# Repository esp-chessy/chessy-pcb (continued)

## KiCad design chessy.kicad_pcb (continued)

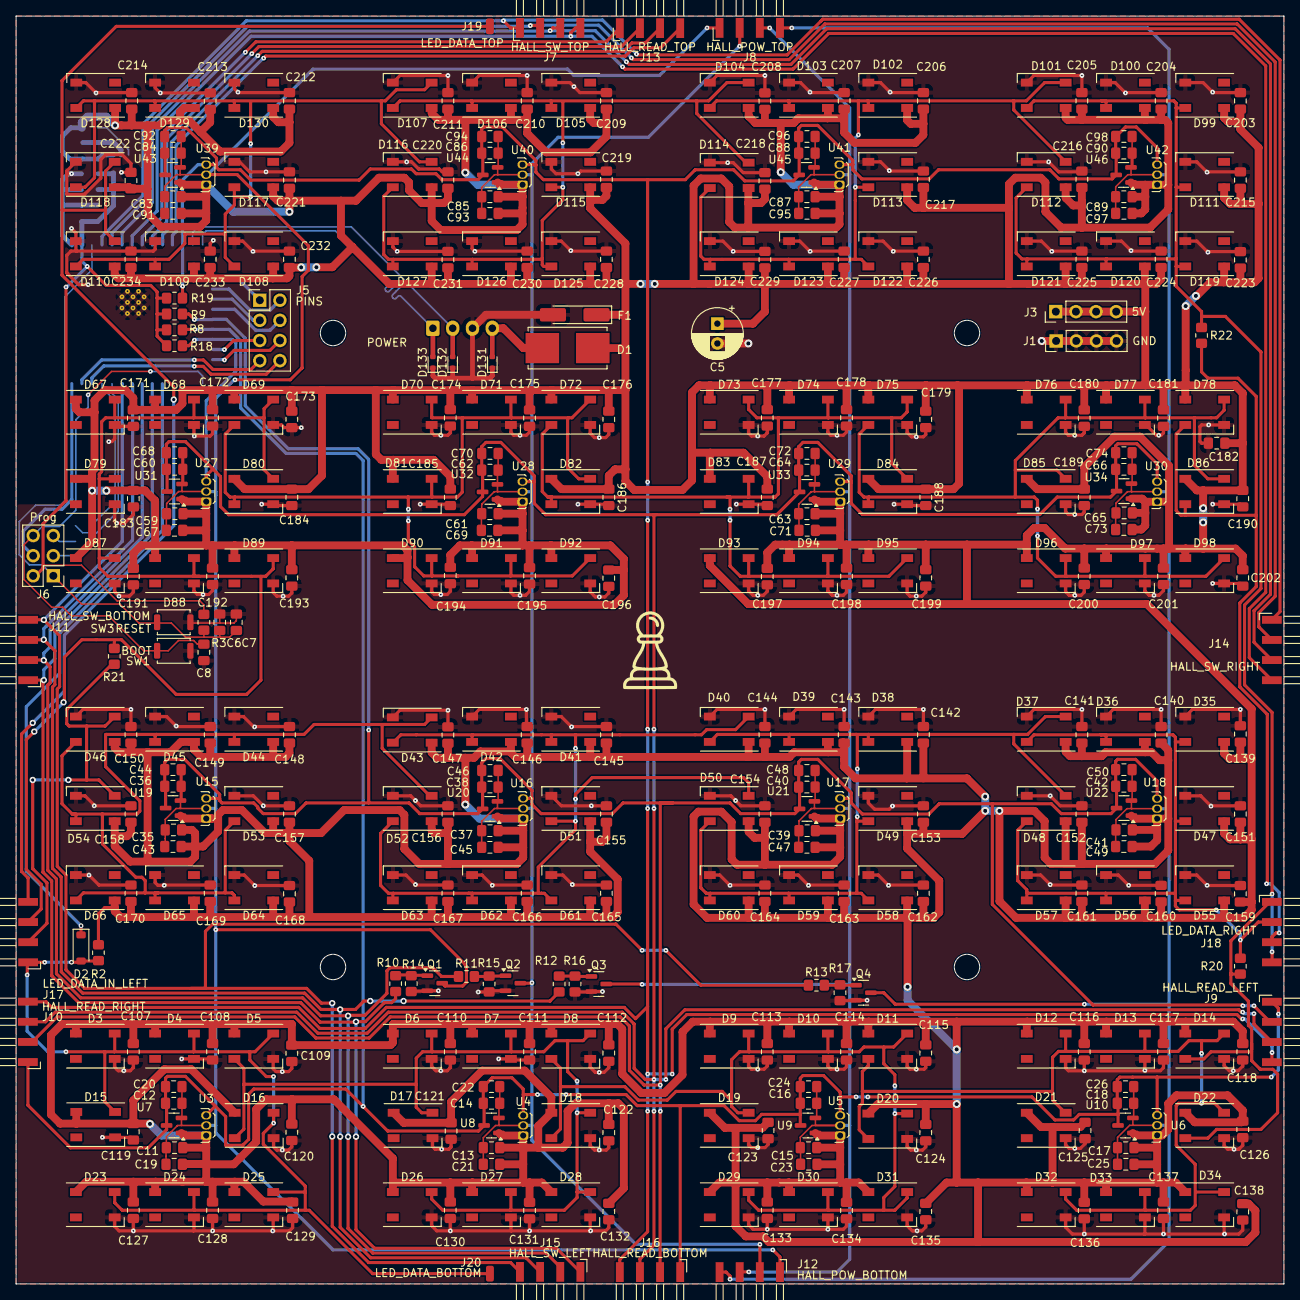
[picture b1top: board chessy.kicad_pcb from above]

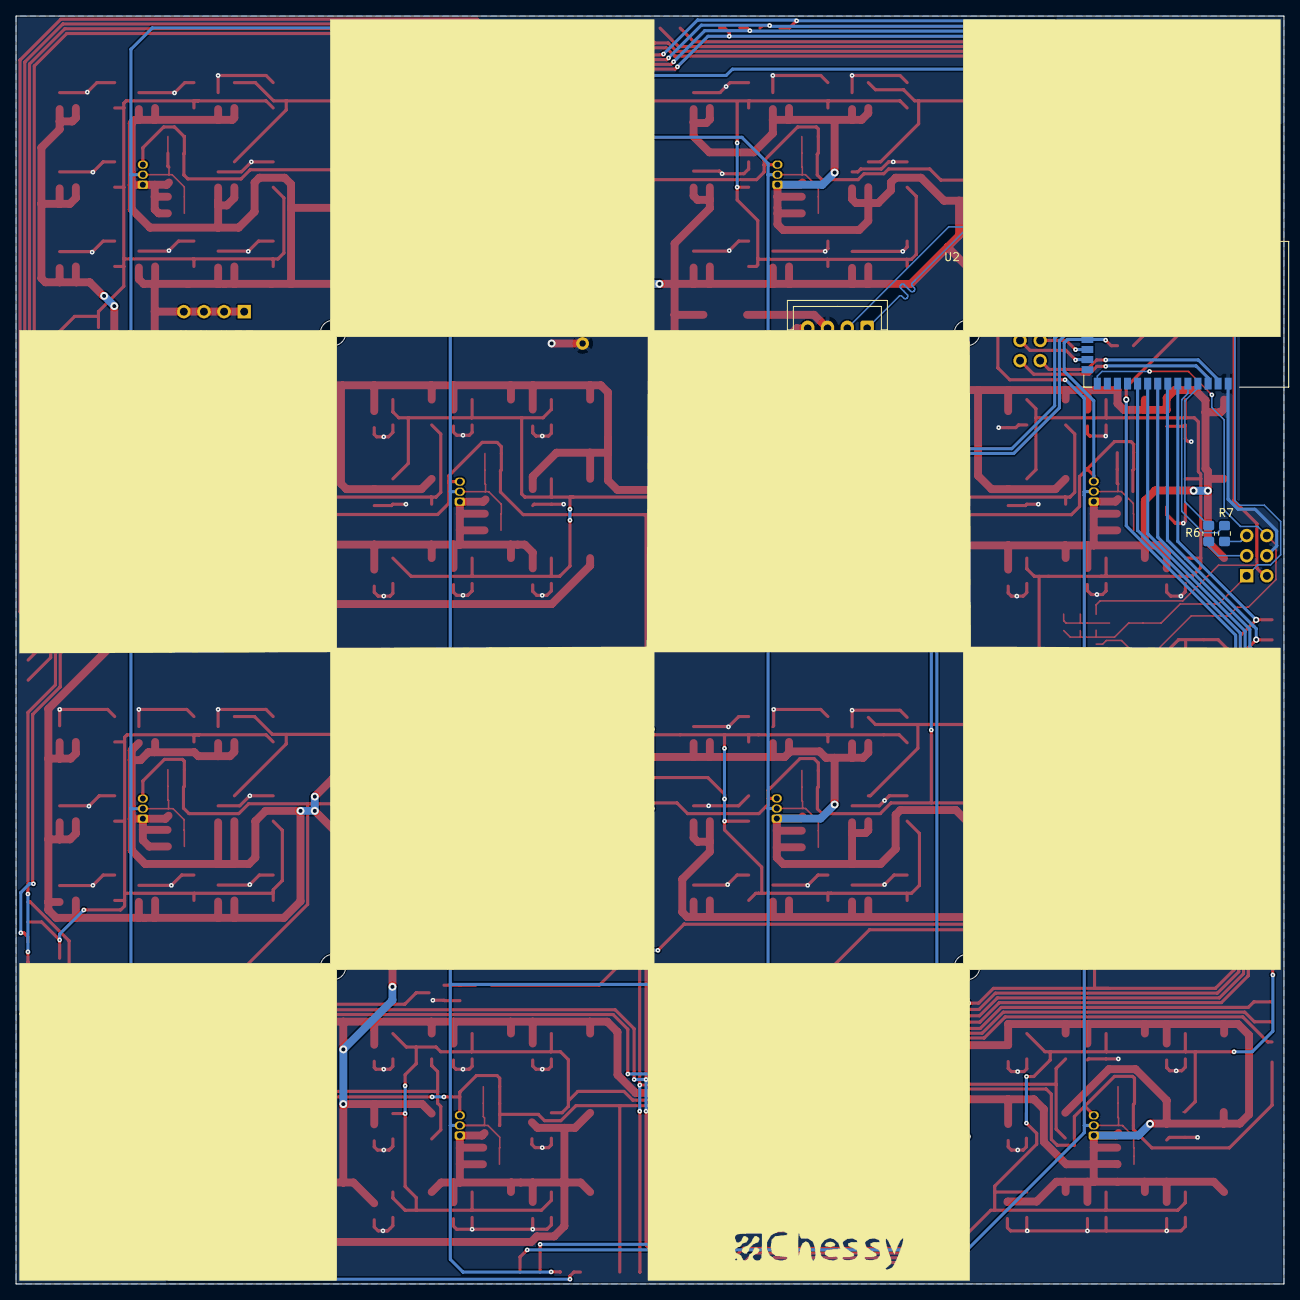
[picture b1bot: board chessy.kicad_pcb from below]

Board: 2 copper layers, 160.0 x 160.0 mm, 415 parts (12 on the bottom side), 66 nets.

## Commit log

2025-02-22 feat: Add first board revision
